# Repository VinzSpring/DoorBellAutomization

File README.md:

# Alfons
## ...a telegram bot and hardware to control old intercoms

The board and software were developed under the following goals:
* Play sounds thru the intercom
* Open the door remotly using an access-token or a telegram-acount whitelist
* Control the hallway's lights
* Detect and answer 'rings'

### 3D-render

### hooked up to RPIZ

### Schematic:

### Board (without ground pane)

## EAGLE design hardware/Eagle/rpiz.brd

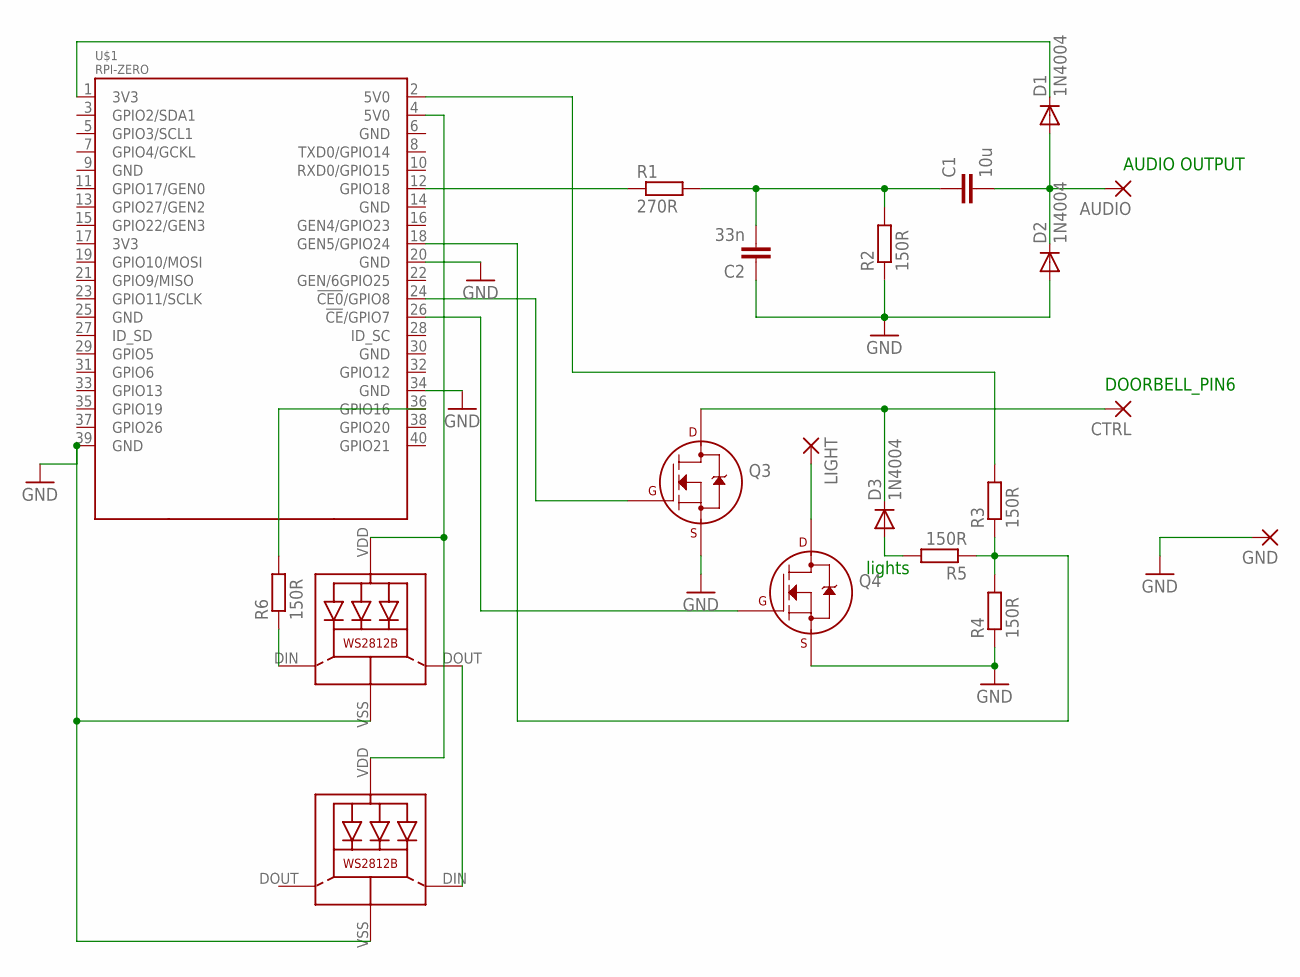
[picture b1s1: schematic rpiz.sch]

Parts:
AUDIO: 2,15/1,0
C1: 10u; C5B3
C2: 33n; C5B3
CTRL: 2,15/1,0
D1, D2, D3: 1N4004; DO41-10
GND: 2,15/1,0
LED1, LED2: WS2812B
LIGHT: 2,15/1,0
Q3, Q4: 2N7000_TO92; TO-92
R1: 270R; 0204/7
R2, R3, R4, R5, R6: 150R; 0204/7
U$1: RPI-ZERO; RASPBERRYPI_BASTELSTUBE_V13_RASPI_BOARD_B+_FULL

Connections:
3V3@1: D1.C, U$1.1 (3V3)
5V0@1: R3.2, U$1.2 (5V0)
5V0@2: LED1.VDD, LED2.VDD, U$1.4 (5V0)
AUDIO_OUT1: AUDIO.1, C1.2, D1.A, D2.C
GND: C2.1, D2.A, GND.1, LED1.VSS (GND), LED2.VSS (GND), Q3.1 (S), Q4.1 (S), R2.1, R4.1, U$1.20 (GND), U$1.34 (GND), U$1.39 (GND)
unnamed: C1.1, C2.2, R1.2, R2.2
unnamed: CTRL.1, D3.C, Q3.3 (D)
unnamed: Q3.2 (G), U$1.24 (!CE0!/GPIO8)
unnamed: R1.1, U$1.12 (GPIO18)
unnamed: R3.1, R4.2, R5.1, U$1.18 (GEN5/GPIO24)
unnamed: D3.A, R5.2
unnamed: Q4.2 (G), U$1.26 (!CE!/GPIO7)
unnamed: LED1.DIN (DI), R6.1
unnamed: LIGHT.1, Q4.3 (D)
unnamed: R6.2, U$1.36 (GPIO16)
unnamed: LED1.DOUT (DO), LED2.DIN (DI)

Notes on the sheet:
AUDIO OUTPUT
DOORBELL_PIN6
lights

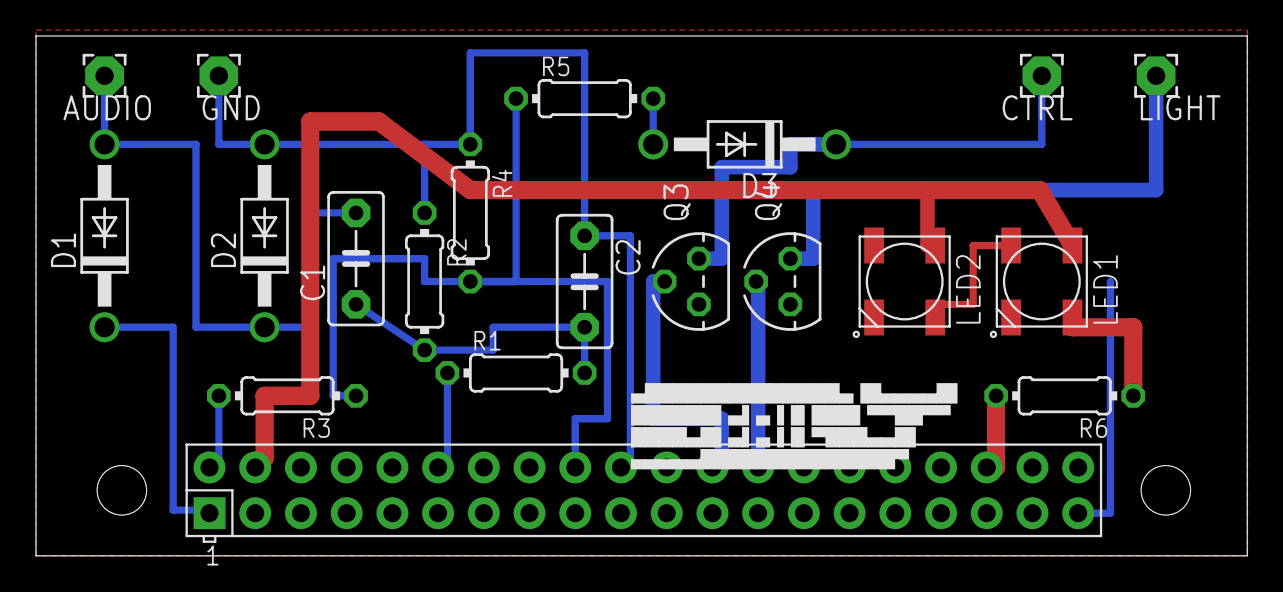
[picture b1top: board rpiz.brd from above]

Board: 2 copper layers, 67.3 x 28.9 mm, 20 parts (0 on the bottom side), 16 nets.

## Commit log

2018-05-08 Added DoorBellController
2018-05-08 Added gitignore
2018-05-09 Added Engine for main-controls
2018-05-09 TokenSystem works
2018-05-09 Adjusted time range for using the token after ringing
2018-05-09 Improved example program variable names
2018-05-09 Optimized Code
2018-05-09 renamed variable, added token generator method
2018-05-09 added hardware
2018-05-15 completed board
2018-06-11 board is now using 2n7000 mosfet, also added 2nd LED
2018-06-11 added imgs
2018-06-11 added img
2018-06-11 Create README.md
    added readme
